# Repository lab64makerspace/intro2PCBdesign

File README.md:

# Introduction to PCB Design
First offered during Winter Quarter AY2018-2019, we're currently updating some material and planning to offer it again during Spring Quarter AY2019-2020.

There are many excellent online tutorials about how to use the various PCB design programs available. This being the case, in this workshop / course we will focus on :
* rapid prototyping of electronics (copper tape on various substrates, "dead-bug" construction, etc.)
* placing some context around PCB design (how & why we make PCBs, various fabrication technologies, etc.)
* building experience with PCB design workflow (by designing & sending boards out for fabrication every week)
* using ancillary tools to ensure form, fit, and function requirements are met
* mastering SMT assembly techniques for prototype / low-volume "in-house" production
* providing entry points to the more "advanced" topics associated with PCB design

If this seems interesting to you, please check out the overview & details page.

We are interested in your feedback! Please send comments, question and suggestions to: lab64ca@ee.stanford.edu

Please use the [issues tab](../../issues) to post questions and answer other students' questions.

Thx,

 Steve
 
 (steven DOT clark AT stanford DOT edu)

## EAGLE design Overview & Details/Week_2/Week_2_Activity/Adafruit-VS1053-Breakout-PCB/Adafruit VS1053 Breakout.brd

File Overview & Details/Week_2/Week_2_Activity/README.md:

## Week_2_Activity Summary

Download the Week_2_Activity folder. 

Open the audio_board.pro file in KiCad

## Add commonly used libraries to your KiCAD libraries
* Follow these instructions to import the Digi-Key KiCad Library: https://forum.digikey.com/t/importing-the-digi-key-kicad-library-into-kicad-5-0-0/4075

## Add Footprints

Open the schematic. 

Select "Tools - Edit Symbol Fields"

Add the footprint for each element. The description section for some of the elements has already been e ntered to help you select the correct footprint. 

<!---
Your symbol fields should look as follows when you're done. </br> 
-->

Select "Apply, Save Schematic & Continue" to save your work. 

## Layout the footprints

Save the schematic and open the pcbnew file. 

Select "Update PCB from schematic" to add the footprints you selected in the previous step to the board layout. 

You should see many white lines connecting the footprints. These are known as net lines and correspond to the electrical connections outlined in your schematic. You now need to strategically arrange the footprints such that you'll be able to add the necessary routes to connect all of the footprints together as dictated by the net lines. **Remember that you should aim to spend 90% of your time creating your footprint layout and only 10% of your time adding traces after you're done the layout.** If you add traces too early, it will be difficult to fix mistakes in your footprint layout. Note that the way components are laid out in a schematic is not always the best way to layout the components on a board. 

When arranging the footprints, here are some things to think about: 

- What size should the board be? 

- Where do you want the connectors to be? 

- How far apart do you want the speakers to avoid crosstalk? 

#### Strategy to layout footprints

Select a pin on a footprint in your pcbnew file and press ~. All of the pins connected to this pin will be highlited. Try doing this for all of the voltage pins (+36V, +12V, +3.3V, +2.5V, +1.8V, GND). If many footprints are connected a specific voltage, consider making a separate plane for that voltage (e.g. ground) and connecting every pin linked to that voltage to the plane through a via. If a few components are connected to a specific voltage, consider arranging them into their own subgroup. Select the optimal layout for the footprints within these subgroups. 

Open both the schematic and pcbnew file at the same time. Select a component on the schematic and notice that its corresponding footprint is highlighted on the pcbnew file. Start making subgroups of footprints by grouping larger components like U1, U2, U3 with their corresponding resistors and capacitors. Select the optimal layout for the footprints within these subgroups.

Some useful commands 

- Hover over a footprint and press R to rotate
- Press X to draw a trace 

Note: aim to get your footprint layout done for this week. We'll critique each other's layout on Wednesday and do the tracing afterwards. 

## Notes from the previous week (we've done these steps for you!) 
This week we are getting ready to layout the Audio Board block. In our weekly activity session Max showed us how to do several things:
1. How to look at the documentation for a part, in this case the Texas Instruments TPA3250 High-Performance Class-D Power Amplifier.
2. How to look through the documentation and find the "eval board" information which gives us a huge head start.
3. How to search for part footprints and install those in the libraries.
4. How to convert a design in Eagle into a KiCAD project by going through the process with the Adafruit VS1053 CODEC Breakout PCB.

### Finding Footprints
Max shared his methodology for finding part footprints. To find part footprints that aren't already in your KiCAD fotprint library he uses the resources below in the order listed:

1.  https://componentsearchengine.com/EXB-18V103JX/Panasonic
2.  https://www.ultralibrarian.com/ {this is a Windows thing, so us Mac folks are outta luck}
3.  https://www.snapeda.com/
4.  https://kcdb.ciphersink.net/
5.  For TI parts: https://webench.ti.com/cad/
6.  Digikey KiCad library: https://www.digikey.com/en/resources/design-tools/kicad
7.  Built-in KiCad libraries are great (and so is the footprint generator)
8.  Importing reference designs and reusing their footprints
9.  If all else fails… google: part number + “footprint” | “PCB” | “component” | “symbol”
10. If you really can't find the correct footprint, try to find a similar component and modify that footprint as required.
11. If you are REALLY stuck you can generate one from scratch* (YIKES!).

<sub> * Yes, we can show you how to do this, but it is time consuming, requires great attention to detail and demands double checking, etc.</sub></br>

We will put more detailed information on each of these steps here as time permits.

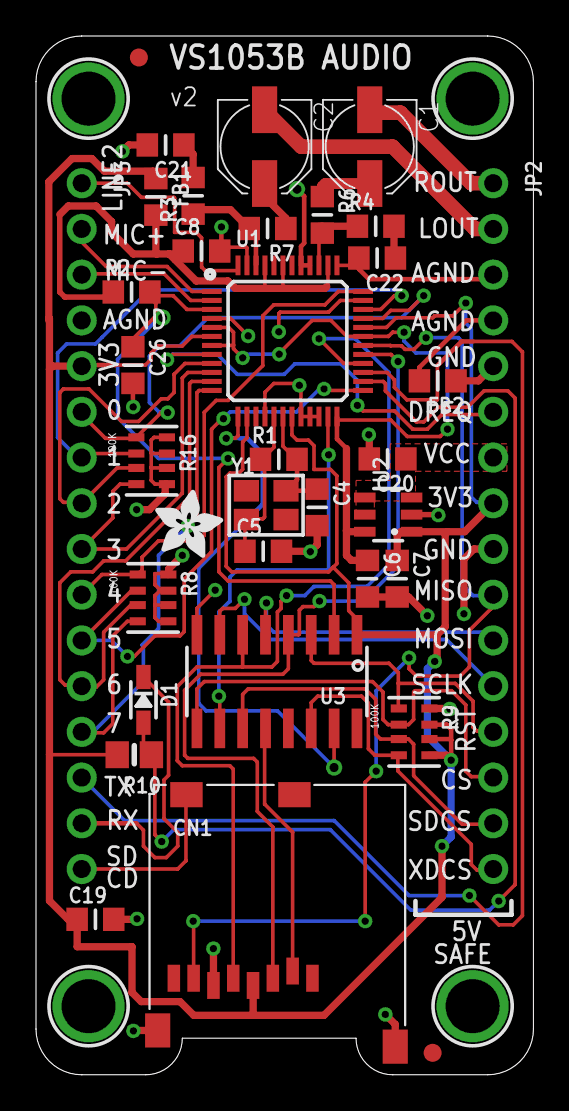
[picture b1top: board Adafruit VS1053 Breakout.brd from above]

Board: 2 copper layers, 27.6 x 57.7 mm, 40 parts (1 on the bottom side), 45 nets.

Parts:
C1, C2: 220uF; PANASONIC_C
C4, C5: 10pF; _0805MP
C6, C7, C19, C20: 10µF; _0805MP
C8, C26: 0.1µF; _0805MP
C21, C22: 10nF (0.01uF); _0805MP
CN1: 2908-05WB-M6; MICROSD
D1: 1N4148; SOD-323
FB1, FB2: FERITTE; _0805MP
FID1, FID2: FIDUCIAL""; FIDUCIAL_1MM
JP2, JP3: 1X16_ROUND
R1: 1M; _0805MP
R2: 100K; _0805MP
R3, R4: 20; _0805MP
R6, R7: 100; _0805MP
R8, R9, R16: 100K; RESPACK_4X0603
R10: 10K; 0805-NO
U1: VS1053B; LQFP48
U2: AP7312-1833W6-7; SOT23-6
U3: 74HC4050D; SOIC16
U$31: ADAFRUIT_3.5MM
U$50, U$51, U$52, U$53: MOUNTINGHOLE3.0THIN; MOUNTINGHOLE_3.0_PLATEDTHIN
U$55: ADAFRUIT_TEXT_20MM
Y1: ABM8G-12.288MHZ-4Y-T3; CRYSTAL_3.2X2.5

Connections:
1.8V: C6.1, U1.5, U1.7, U1.24, U1.31, U2.6
3.3V: C7.1, C19.1, CN1.4, FB1.1, JP2.8, JP3.5, R9.5, R9.6, R9.7, R10.2, U1.6, U1.14, U1.19, U1.32, U2.1, U3.1
AGND: C8.2, C21.2, C22.2, FB2.2, JP2.3, JP2.4, JP3.4, U1.37, U1.40, U1.41, U1.47
AVDD: C8.1, FB1.2, R2.1, U1.38, U1.43, U1.45
CS_3V: U1.23, U3.10
CS_5V: JP2.14, R9.2, U3.9
DREQ: JP2.6, U1.8
GND: C4.2, C5.2, C6.2, C7.2, C19.2, C20.2, C26.2, CN1.6, CN1.MT1, CN1.MT2, FB2.1, JP2.5, JP2.9, R8.5, R8.6, R8.7, R8.8, R9.8, R16.5, R16.6, R16.7, R16.8, U1.4, U1.16, U1.20, U1.21, U1.22, U1.35, U2.2, U3.8
GPIO0: JP3.6, R16.1, U1.33
GPIO1: JP3.7, R16.2, U1.34
GPIO2: JP3.8, R16.3, U1.9
GPIO3: JP3.9, R16.4, U1.10
GPIO4: JP3.10, R8.1, U1.36
GPIO5: JP3.11, R8.2, U1.25
GPIO6: JP3.12, R8.3, U1.11
GPIO7: JP3.13, R8.4, U1.12
LEFT: R3.1, R7.2, U1.46
LEFT_FILTERED: C2.+, R7.1
LINE2: JP3.1, U1.48
L_OUT: C2.-, JP2.2
MIC_N: JP3.3, U1.2
MIC_P: JP3.2, U1.1
MISO: CN1.7, JP2.10, U1.30
MOSI_3V: CN1.3, U1.29, U3.4
MOSI_5V: JP2.11, U3.5
unnamed: C5.1, R1.1, U1.17, Y1.1
unnamed: C4.1, R1.2, U1.18, Y1.2
unnamed: C21.1, R3.2
unnamed: C22.1, R4.2
RIGHT: R4.1, R6.2, U1.39
RIGHT_FILTERED: C1.+, R6.1
RST_3V: C26.1, R2.2, U1.3, U3.2
RST_5V: JP2.13, R9.1, U3.3
RX: D1.A, R10.1, U1.26
RX_5V: D1.C, JP3.15
R_OUT: C1.-, JP2.1
SCLK_3V: CN1.5, U1.28, U3.6
SCLK_5V: JP2.12, U3.7
SDCS_3V: CN1.2, U3.12
SDCS_5V: JP2.15, R9.3, U3.11
SD_DETECT: CN1.CD1, JP3.16
TX: JP3.14, U1.27
VIN: C20.1, JP2.7, U2.3, U2.4, U2.5
XDCS_3V: U1.13, U3.15
XDCS_5V: JP2.16, R9.4, U3.14

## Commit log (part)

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2020-03-30 Adding screenshots for inkscape board outline
2020-03-30 Inkscape board outline instructions
2020-03-30 Added inkscape tutorial images
2020-03-30 Fixed image paths
2020-03-30 Added onshape screenshots
2020-03-30 Added instructions for onshape
2020-03-30 Added board outline instructions link
2020-03-30 fixed USB-C image links
2020-03-30 added img abt annular ring
2020-03-30 added img abt annular ring link
2020-03-31 USB-C Schematic changes
2020-03-31 USB-C Images
2020-03-31 update USB-C readme
2020-03-31 edited symbol for usb-c
2020-03-31 update pcb for usb type C
2020-03-31 Add images for USB-C PCB
2020-04-02 Update README.md
    wk 1 activity
2020-04-02 Update README.md
    glossary
2020-04-02 Update README.md
    finished glossary. added some terms
2020-04-02 added image for plated through-hole padstack
2020-04-02 Removed duplicate content
2020-04-02 Added discussion questions
2020-04-02 Added info on CAD and outlines
2020-04-02 Added clarification on assembly
2020-04-02 Added info on why use CAD
2020-04-02 Update README.md
    added line break before image
2020-04-02 added picture for symbol footprint linking
2020-04-03 Sync'ing up my version
2020-04-03 Update README.md
    fixed broken links
2020-04-03 correct USB-C readme! No downloads
2020-04-04 Update README.md
    updated link to schematic
2020-04-04 made hierarchical schematic for display board. converted adafruit EAGLE CAD projects for TFT LCD display and STMPE811 into KiCad format. Added display and STMP schematics into root schematic
2020-04-04 added KiCad-ready LCD and controller projects from Adafruit
2020-04-05 made connections local to the STMPE811. removed TFT_LCD schematic. annotated schematic
2020-04-05 added hierarchical lables
2020-04-05 added picture
2020-04-05 brought LED display symbol into schematic hierarchy
2020-04-05 added 50 position FFC connector. assigned nets b/t FFC connector and display board
2020-04-05 removed .zip
2020-04-05 added STEMP811 controller and added pins
2020-04-05 added hierarchical pins to STMPE811
2020-04-05 added todo note on schematic
2020-04-05 linked symbol to footprint for 50pin connector and controller
2020-04-05 generated PDF of the adafruit STMPE610
2020-04-05 Add digikey kicad library inst
2020-04-05 Added footprint for SN74LVC245ADBR
2020-04-05 Added symbol/footprint for LP2985-28DBVR
2020-04-05 Added footprint for APX803S
2020-04-05 made activity3.lib. 50pin connector, LCD display, LDO regulator, SN74, and controller all in it
2020-04-05 added activity3.pretty. 50pin connector footprint and controller footprint included.
2020-04-05 updated Week 2 README
2020-04-05 Added board description
2020-04-05 renamed activity3 files to display_board files
2020-04-05 updated directories
2020-04-05 made PDF folder
2020-04-05 Restructured repo
2020-04-05 Fixed links
2020-04-06 First pass at power board content
2020-04-06 updated displayboard readme.
2020-04-06 fixed symbol/footprint paths for displayboard
2020-04-06 Added footprints to audioboard
2020-04-06 Update power board readme
2020-04-07 minor
2020-04-07 created footprint for circular pins for sam32 and linked to symbols. linked displayboard's lcd screen to the 50pin connector footprint
2020-04-07 Added video link
2020-04-07 Restructured setup content
2020-04-07 Restructured setup readme's
2020-04-09 finished assigning audioboard footprints
2020-04-09 added footprints for square stackable pins (for sam32)
2020-04-09 made .pretty folder for audio board and sam32 pin socket footprints
2020-04-09 removed 4John folder. kept zip
2020-04-09 audio board fixes
2020-04-09 audio board error fixes
2020-04-09 audio board lib file fixes
2020-04-09 fixed footprint/symbol link for the MAX1735EUK25. created .pretty folder for AudioBoard footprints. the 1x10 pin connector for the sam32 still needs a footprint. the footprints for the phoenix conenc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
2020-04-09 foottprintt instrtuctions
2020-04-09 Readme perfection
2020-04-09 Increased readme perfection
2020-04-09 Increased increased readme perfection
2020-04-10 testing a push to the public github repo
2020-04-10 wrote instructions on how to push to the github
2020-04-10 Fixed another link
2020-04-11 added a guide on converting SVG files from Inkscape into DXF files for KiCad
2020-04-11 syncing with github
2020-04-12 Took out instruction
2020-04-14 Standardized CAD instructions
2020-04-14 Standardized discussion section
2020-04-14 Clarified two connector option
2020-04-14 Minor change
2020-04-14 Added submission instructions
2020-04-17 added public version of LED_Board
2020-04-17 Added fiducials instructions
2020-04-17 Added image
2020-04-18 Adding MCPCB image
2020-04-18 Saving changes
2020-04-18 Adding via instructions
2020-04-18 Added schematic image
2020-04-18 Updated LED activity
2020-04-18 Adding led tower image
2020-04-18 Adding intro
2020-04-18 Reordered items
2020-04-18 Fixed typo
2020-04-19 Added ERC explanation
2020-04-19 Added schematic info
2020-04-19 Update README.md
    LED Board content
2020-04-19 Add instructions about Python script
2020-04-19 Fix formatting
2020-04-20 Added silkscreen photos
2020-04-20 Update silkscreen
2020-04-20 Added connector flip
2020-04-20 Minor update
2020-04-20 Adding routing images
2020-04-20 Add image
2020-04-20 added thermal relief
2020-04-20 Added filled zones
2020-04-21 Updated schedule
2020-04-21 Removed erroneous ground plane
2020-04-21 Add small note about filled zones
2020-04-21 Minor edit
2020-04-21 Update README.md
    minor spacing change
2020-04-22 Updated content
2020-04-24 bad pcb examples
2020-04-24 parting thoughts
2020-04-24 Add mounting hole placement
2020-04-24 added pics of art of electronics
2020-04-24 Add mounting hole script
2020-04-24 Add mounting hole picture
2020-04-26 Added net class clearance
2020-04-26 added jlcpcb
2020-04-26 Fixed error
2020-05-01 power board schematic
2020-05-01 power board considerations
2020-05-01 powerboard
2020-05-01 powerboard content
2020-05-01 LDO datasheet
2020-05-01 removed portion for acitivty and fixed libraries
2020-05-01 activity
2020-05-01 activity finalizing
2020-05-01 Update instructions
2020-05-01 Update README.md
    increased perfection
2020-05-03 Update via tenting issue
2020-05-03 Update symbol picture
2020-05-03 +5VR
2020-05-03 final
2020-05-03 change to input
2020-05-03 change to input correct
2020-05-03 Bolded
2020-05-03 SubmissionImages
2020-05-03 MaskImages
2020-05-03 Added submission instruc
2020-05-03 Fixed images
2020-05-08 Create instructions_in_progresss
2020-05-08 More instructions
2020-05-08 Add power board outline
2020-05-08 Add four layers picture
2020-05-08 Begin instructions fork. Add board setup screenshot.
2020-05-08 Adding screenshots
2020-05-08 Add suggested floorplan image
2020-05-08 Add footprint layout tips
2020-05-08 Fix image
2020-05-08 Create part 1
2020-05-08 Merging activity files
2020-05-08 Add pictures
2020-05-08 Add step 0
2020-05-08 Minor edits
2020-05-08 Add more tips
2020-05-08 More tips
2020-05-08 More images
2020-05-08 Add advice
2020-05-08 More edits
2020-05-08 Update content
2020-05-08 Fix link
2020-05-08 Adding footprints
2020-05-09 inductor footprints
2020-05-09 Update README.md
    inductor footprints
2020-05-09 Add files via upload
    22uH footprint
2020-05-09 Adding updated footprints
2020-05-10 Add silkscreen
2020-05-11 added diode footprint
2020-05-11 changed image
2020-05-12 displayboard WIP
2020-05-12 Start layer numbering instructions
2020-05-12 Add images
2020-05-12 More layer numbering
2020-05-12 Minor changes
2020-05-13 Update layer numbering explanation
2020-05-13 Add annotated schematic
2020-05-13 Added annotated schematic
2020-05-13 Add Mounting Holes
2020-05-13 Add python script
2020-05-13 Add mounting hole instructions
2020-05-15 Add CAD
2020-05-15 Update README.md
    bypass caps
2020-05-16 Removed lines from capacitor footprint
2020-05-16 Create summary
2020-05-16 Edit
2020-05-16 Update with feedback
2020-05-16 Add vias
2020-05-16 new symbol
2020-05-16 new footprint
2020-05-17 fixed diode
2020-05-22 new display files
2020-05-22 Initial symbol instructions
2020-05-22 Add pin types
2020-05-22 created connector
2020-05-22 labels added. Go ham
2020-05-27 Attempt at adding Steve's schematic into Root.sch
2020-05-27 Oops removed hierarchical sheet
2020-05-27 Updated with Marion's footprints
2020-05-27 Use hand_solder footprints
2020-05-27 I forgot to save...
2020-05-27 Add new symbols to library with a different name
2020-05-27 Modify sym-lib-table to match instructions
2020-05-28 Added board outline
2020-05-28 Adding mounting hole
2020-05-28 Adding python script
2020-05-29 Add photos
2020-05-29 Add displayboard instructions
2020-05-29 Small changes
2020-05-29 Add connected display symbol picture
2020-05-29 Add hierarchical schematic
2020-05-29 Hierarchical labels instructions
2020-05-30 Add cutout zone image
2020-05-30 Add note about tracing cutout zone
2020-05-31 Add file
2020-09-26 Update README.md
    removed usb C from options pending fix
2020-09-28 Corrected USB-C footprint
2020-12-02 Added meeting recordings
